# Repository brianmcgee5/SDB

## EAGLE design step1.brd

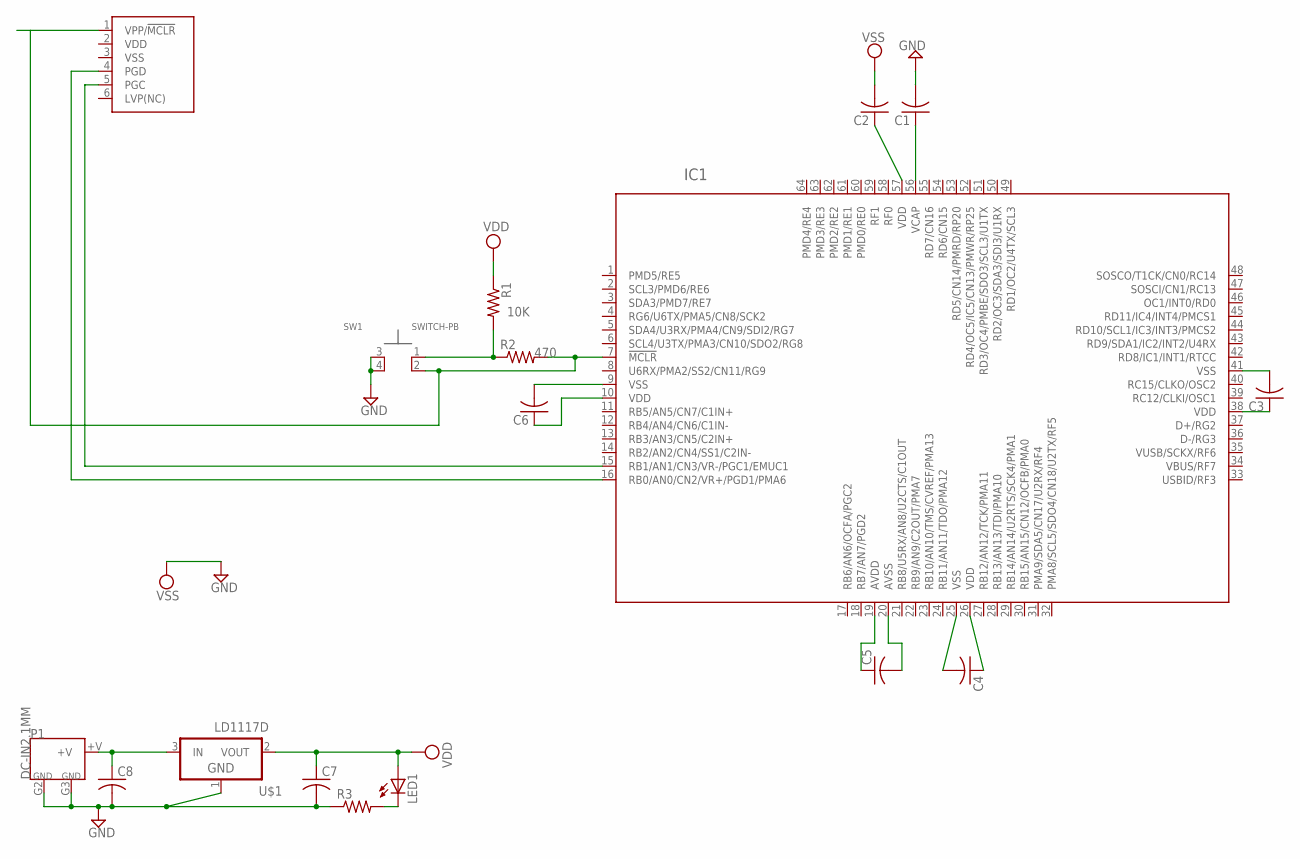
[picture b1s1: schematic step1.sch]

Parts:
C1: C-USC1206; C1206
C2, C3, C4, C5, C6: C-USC0805; C0805
C7, C8: C-USC0603; C0603
IC1: PIC32MX795; TQFP64-10X10RMS
LED1: LEDSMT1206; 1206
P1: DC-IN2.1MM; DC-POWERJACK
R1, R2: R-US_R0603; R0603
R3: R-US_R0805; R0805
SW1: SWITCH-PB; PBSWITCH
U$1: LD1117D; DPAK
U$2: PICKIT3

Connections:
+V: C8.1, P1.+V, U$1.3 (IN)
GND: C1.2, C7.2, C8.2, P1.G2, P1.G3, R3.1, SW1.3, SW1.4, U$1.1 (GND), U$2.3 (VSS)
unnamed: R1.2, R2.1, SW1.1
unnamed: IC1.7 (!MCLR), R2.2, SW1.2, U$2.1 (VPP/!MCLR)
unnamed: C1.1, IC1.56 (VCAP)
unnamed: C2.1, IC1.57 (VDD)
unnamed: C3.2, IC1.41 (VSS)
unnamed: C3.1, IC1.38 (VDD)
unnamed: C4.2, IC1.25 (VSS)
unnamed: C4.1, IC1.26 (VDD)
unnamed: C5.1, IC1.19 (AVDD)
unnamed: C5.2, IC1.20 (AVSS)
unnamed: C6.2, IC1.9 (VSS)
unnamed: C6.1, IC1.10 (VDD)
unnamed: LED1.C, R3.2
unnamed: IC1.15 (RB1/AN1/CN3/VR-/PGC1/EMUC1), U$2.5 (PGC)
unnamed: IC1.16 (RB0/AN0/CN2/VR+/PGD1/PMA6), U$2.4 (PGD)
VDD: C7.1, LED1.A, R1.1, U$1.2 (VOUT), U$2.2 (VDD)
VSS: C2.2

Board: 2 copper layers, 17 parts (0 on the bottom side), 18 nets, no tracks yet.
